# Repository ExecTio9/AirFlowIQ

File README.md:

# AirFlowIQ

> **Full-Stack HVAC Monitoring Platform**  
> Embedded Hardware • Edge Firmware • Cloud Dashboard

AirFlowIQ is an integrated HVAC monitoring system designed to provide real-time environmental visibility, airflow analytics, and filter identification inside residential and commercial HVAC systems.

The platform combines embedded sensing hardware, dual-transport communication (WiFi + LoRa), and cloud-connected dashboard infrastructure for reliable field deployment and remote monitoring.

---

## 🚀 Platform Overview

AirFlowIQ integrates:

- 📡 **Dual Communication** — WiFi with automatic LoRa fallback  
- 🌡️ **Environmental Monitoring** — Temperature, Humidity, Pressure  
- 🌬️ **Airflow Velocity Measurement**  
- 🪪 **RFID-Based Filter Identification**  
- 🔋 **Battery Voltage Monitoring**  
- 🟢 **Embedded RGB Diagnostic System**  
- ☁️ **Cloud Logging & Dashboard Infrastructure**

Designed for:

- Residential HVAC monitoring  
- Commercial service deployments  
- Technician-friendly installation  
- Remote fleet management  

---

## 🏗 System Architecture
Sensors → ESP32 Sensor Node → WiFi / LoRa → ESP32 Hotspot Gateway → Cloud Backend → Dashoboard

### Sensor Node

- ESP32-C6
- BME280 (Temperature / Humidity / Pressure)
- MFRC522 (RFID Filter Identification)
- Brushless fan airflow sensor
- ADC-based battery monitoring
- RFM95 LoRa module
- RGB LED diagnostics
- USB service mode

### Gateway Node

- ESP32-C3 / C6
- WiFi Access Point
- LoRa Receiver
- Cloud forwarding service
- Diagnostic handshake capability

---

## 📁 Repository Structure
```text
AirFlowIQ/
├── firmware/
│ ├── sensor_node/
│ ├── gateway_node/
│
├── hardware/
│ ├── pcb/
│ ├── schematics/
│ └── bom/
│
├── dashboard/
│
├── google_scripts/
│
├── docs/
│ ├── architecture/
│ ├── testing/
│ ├── compliance/
│ └── archive/
│
└── README.md
```

---

## 📊 Data Model

| Field | Description |
|--------|------------|
| `id` | Device identifier |
| `boot_count` | Power cycle counter |
| `battery_voltage` | Battery level (V) |
| `sensor_status` | Sensor health indicator |
| `temperature` | °C |
| `humidity` | % Relative Humidity |
| `pressure` | hPa |
| `wind_speed` | Derived airflow velocity |
| `rfid` | Filter UID |

---

## 🛠 Field Installation

1. Mount Sensor Node inside HVAC unit.
2. Install airflow sensor across duct path.
3. Attach RFID tag to filter.
4. Power node (battery or USB).
5. Pair with Gateway (WiFi or LoRa).
6. Confirm data visibility on dashboard.

---

## 🟢 Embedded Diagnostics

Diagnostic mode is triggered via USB connection.

### Sensor Status

| Color | Meaning |
|-------|----------|
| Green | All sensors operational |
| Yellow | Environmental sensor only |
| Blue | RFID only |
| Red | Sensor failure |

### Battery Status

| Color | Meaning |
|-------|----------|
| Green | > 75% |
| Yellow | 40–75% |
| Red | < 40% |

### Communication Status

| Color | Meaning |
|-------|----------|
| Green | WiFi active |
| Blue | LoRa active |
| Red | Offline |

---

## 💻 Development Setup

### Requirements

- Arduino IDE or PlatformIO  
- ESP32 board support (C3 / C6)  
- Required libraries:
  - Adafruit_BME280  
  - MFRC522  
  - RadioHead (RH_RF95)  
  - WiFiManager (optional)

### Flashing Firmware

```bash
esptool.py --port COMx --baud 460800 write_flash 0x10000 firmware.bin

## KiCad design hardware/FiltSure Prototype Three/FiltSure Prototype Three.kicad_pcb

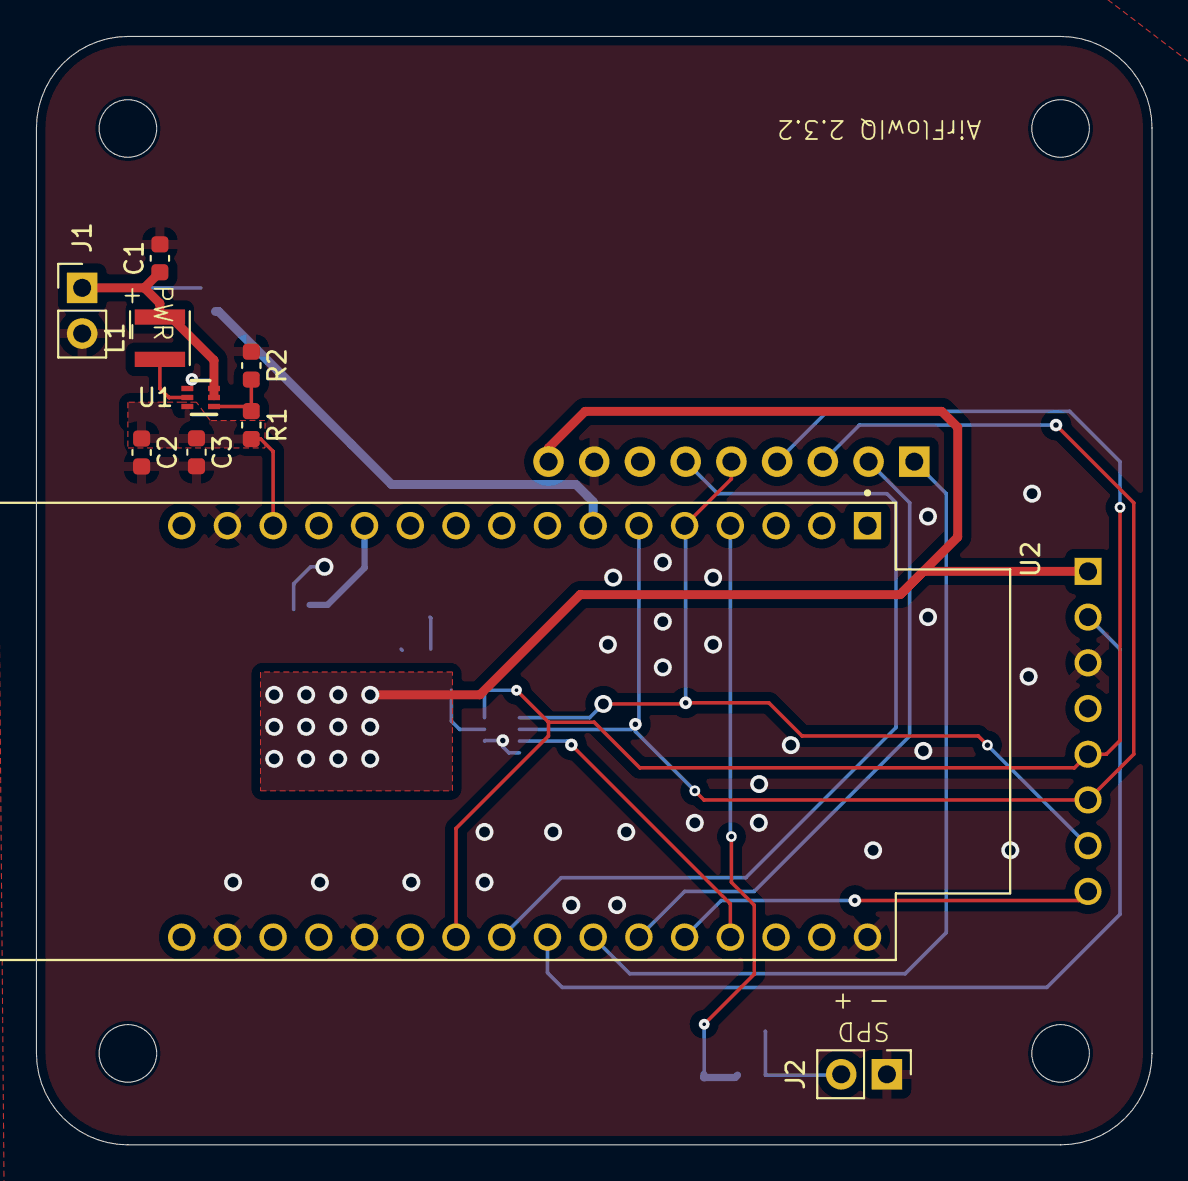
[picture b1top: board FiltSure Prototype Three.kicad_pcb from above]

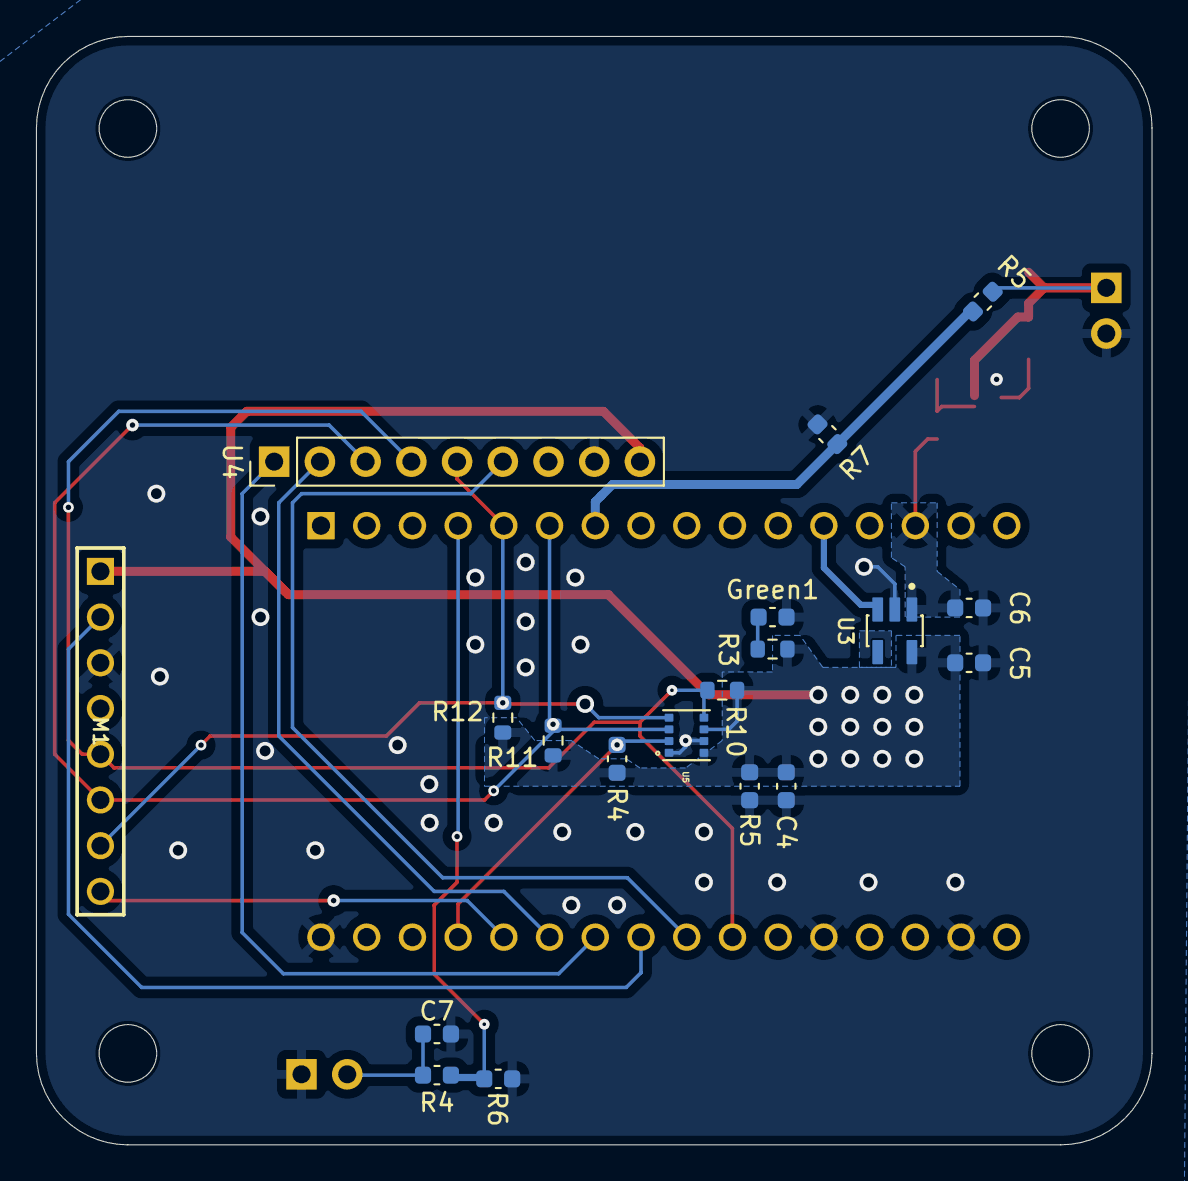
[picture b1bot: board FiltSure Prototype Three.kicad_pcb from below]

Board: 2 copper layers, 62.0 x 61.6 mm, 33 parts (19 on the bottom side), 20 nets.

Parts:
C1, C5, C6, C7: 10uF; C_0603_1608Metric
C2, C3: 22uF; C_0603_1608Metric
C4: 100nF; C_0603_1608Metric
Green1: LED; C_0603_1608Metric
H1, H2, H3, H4: MountingHole; MountingHole_3.2mm_M3
J1, J2: Conn_01x02_Socket; PinHeader_1x02_P2.54mm_Vertical
L1: SRP6530A-1R0M; L_Wurth_WE-LQSH-3012
M1: RFID-RC522
R1: 732k; C_0603_1608Metric
R2: 100k; C_0603_1608Metric
R3, R10, R11, R12: 10k; R_0603_1608Metric
R4, R4#2, R5, R5#2, R6, R7: 10k; C_0603_1608Metric
U1: TPS61023DRLR; DRL0006A
U2: ESP32-C6-DEVKITC-1-N8; MODULE_ESP32-C6-DEVKITC-1-N8
U3: AP2112K-3.3TRG1; SOT95P285X140-5N
U4: RFM95W-868S2; PinHeader_1x09_P2.54mm_Vertical
U5: BME280; PSON65P250X250X100-8N

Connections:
+3.3V: C4.1, C5.1, M1.8 (3V3), R3.1, R4.1, R5#2.1, R10.1, R11.1, R12.1, U3.5 (VOUT), U4.13 (3_3V), U5.6 (VDDIO), U5.8 (VDD)
+5V: C2.1, C3.1, C6.1, R1.2, U1.6 (VOUT), U2.J1_14 (VCC_5V), U3.1 (VIN)
/Batt_Pin: R5.2, R7.1, U2.J1_7 (GPIO0)
/CS_BME: R4.2, U2.J3_4 (GPIO15), U5.2 (CSB)
/CS_LoRa: U2.J3_6 (GPIO22), U4.5 (NSS)
/CS_RFID: M1.1 (SDA), U2.J3_5 (GPIO23)
/CS_VREG: U2.J1_12 (GPIO2), U3.3 (EN)
/IRQ_LoRa: U2.J3_9 (GPIO19), U4.14 (DIO0)
/MISO: M1.4 (MISO), R10.2, U2.J3_10 (GPIO18), U4.3 (MOSI), U5.5 (SDO)
/MOSI: M1.3 (MOSI), R11.2, U2.J1_6 (GPIO7), U4.2 (MISO), U5.3 (SDI)
/RFID_RST: M1.7 (RST), U2.J3_8 (GPIO20)
/RST_LoRa: U2.J3_7 (GPIO21), U4.6 (RESET)
/SCK: M1.2 (SCK), R12.2, U2.J1_5 (GPIO6), U4.4 (SCK), U5.4 (SCK)
/Speed_Pin: R4#2.2, R6.1, U2.J1_4 (GPIO5)
GND: C1.2, C2.2, C3.2, C4.2, C5.2, C6.2, C7.2, Green1.1 (K), J1.2, J2.1, M1.6 (GND), R2.1, R5#2.2, R6.2, R7.2, U1.4 (GND), U2.J1_15 (GND_J1_15), U2.J3_1 (GND_J3_1), U2.J3_12 (GND_J3_12), U2.J3_15 (GND_J3_15), U3.2 (GND), U4.8 (GND@1), U5.1 (GND), U5.7 (GND)
unnamed: Green1.2 (A), R3.2
unnamed: C7.1, J2.2, R4#2.1
unnamed: R1.1, R2.2, U1.1 (FB)
unnamed: L1.1, U1.5 (SW)
VCC: C1.1, J1.1, L1.2, R5.1, U1.2 (EN), U1.3 (VIN)

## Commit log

2025-09-15 updated relay framework
2025-10-13 Create CODEOWNERS (#3)
    good
2025-10-13 Create pull_request_template.md (#4)
2025-12-12 Create AirflowIQ
2026-02-11 cleanup
2026-02-11 data dump + hardware update
2026-02-11 data fix
2026-02-11 Added all the dashboard code
2026-02-16 RFID FIX

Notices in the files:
parts and their libraries:
COPYRIGHT: Copyright (C) 2022 Ultra Librarian. All rights reserved.
